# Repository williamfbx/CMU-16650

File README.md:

# Systems Engineering and Management for Robotics
Subject Name: Systems Engineering and Management for Robotics  
Subject Code: 16650-A  
Semester Taken: Fall 2024  
Instructor: Dimi Apostolopoulos  
Grade: A+  
Difficulty: 2/5

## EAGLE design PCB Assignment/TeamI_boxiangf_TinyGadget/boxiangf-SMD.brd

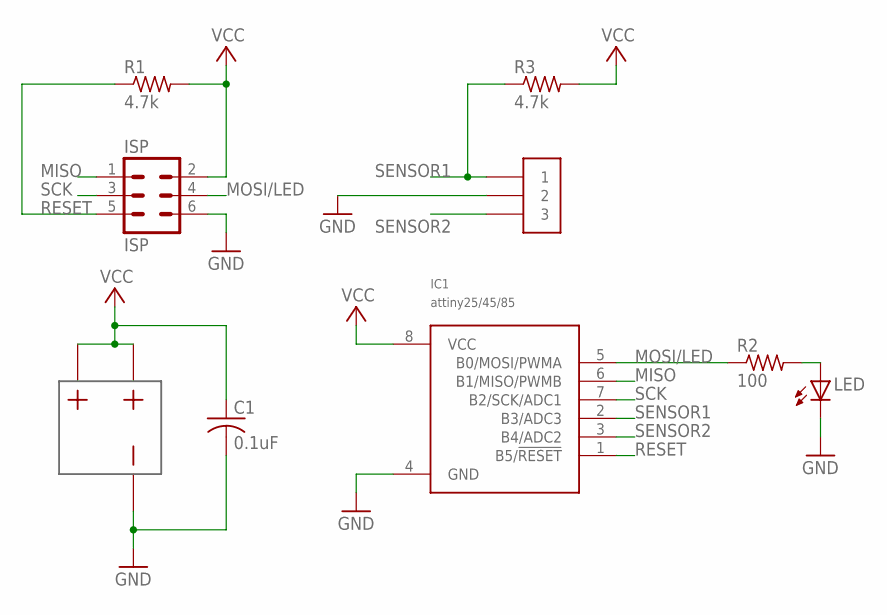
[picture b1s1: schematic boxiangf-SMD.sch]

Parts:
C1: 0.1uF; C0402
IC1: attiny25/45/85; 8S1
ISP: ISP; SM6PIN
LED: LEDSMLED; CHIPLED_0603
R1, R3: 4.7k; R0402
R2: 100; R0402
SENSE: 3PINCONSM_3PIN; SM3PIN
US1: BATTERYSM_BA2032; BA2032SM

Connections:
GND: C1.2, IC1.4 (GND), ISP.6, LED.C, SENSE.2, US1.1
MISO: IC1.6 (B1/MISO/PWMB), ISP.1
MOSI/LED: IC1.5 (B0/MOSI/PWMA), ISP.4, R2.1
unnamed: LED.A, R2.2
RESET: IC1.1 (B5/!RESET), ISP.5, R1.1
SCK: IC1.7 (B2/SCK/ADC1), ISP.3
SENSOR1: IC1.2 (B3/ADC3), R3.1, SENSE.1
SENSOR2: IC1.3 (B4/ADC2), SENSE.3
VCC: C1.1, IC1.8 (VCC), ISP.2, R1.2, R3.2, US1.2, US1.3

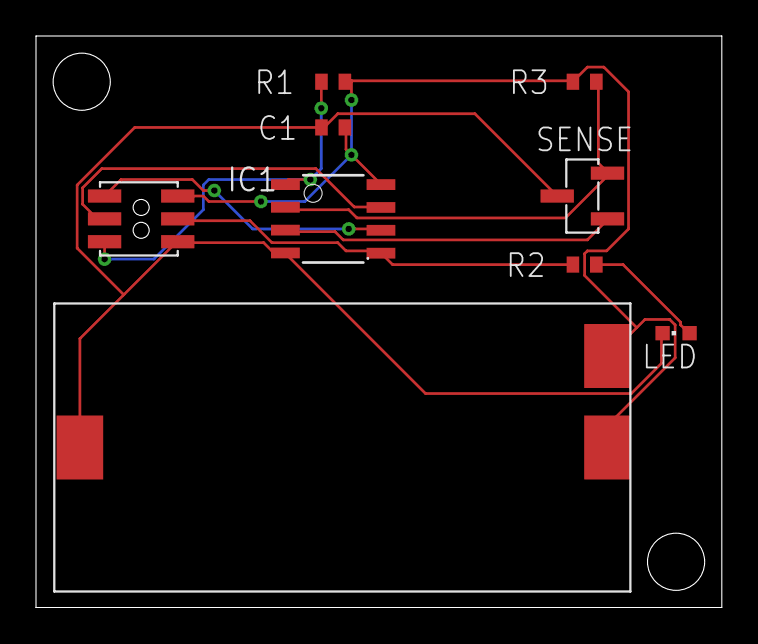
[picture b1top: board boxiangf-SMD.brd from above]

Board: 2 copper layers, 38.1 x 31.8 mm, 9 parts (0 on the bottom side), 9 nets.
